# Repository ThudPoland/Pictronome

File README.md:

Metronome based on PIC16F microcontroller.

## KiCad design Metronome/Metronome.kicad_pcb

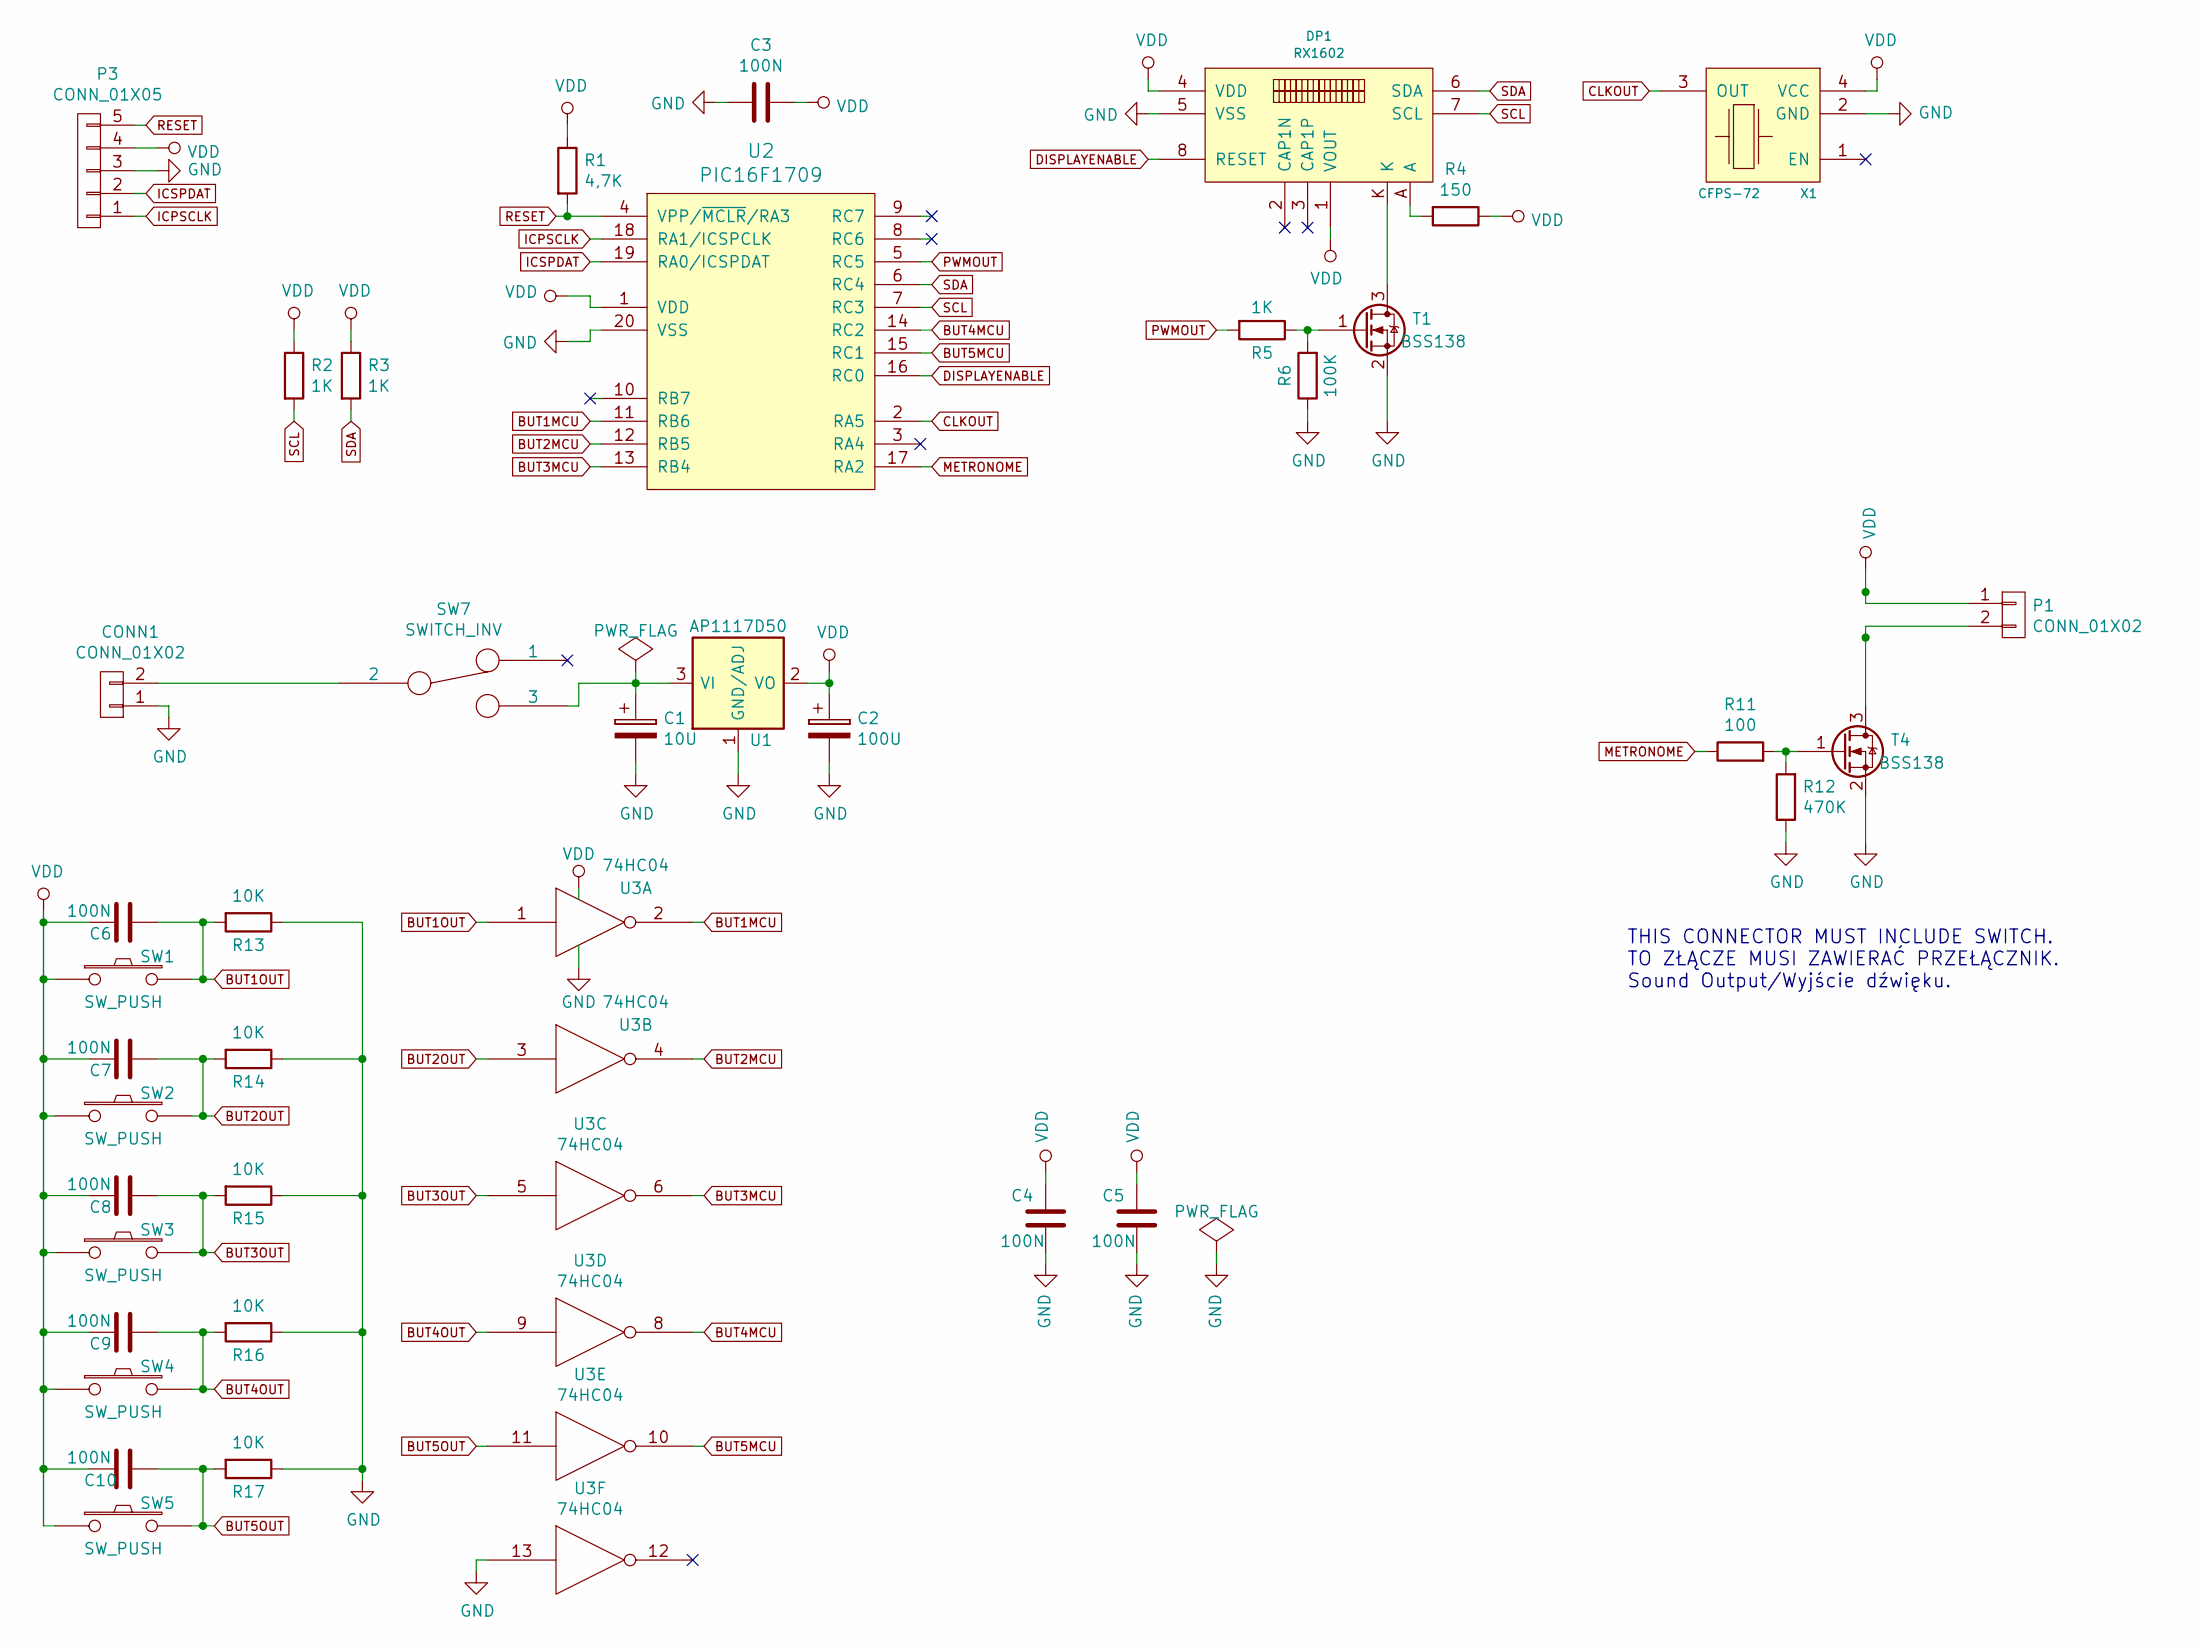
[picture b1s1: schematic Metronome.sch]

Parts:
C1: 10U; C_1206_HandSoldering
C2: 100U; TantalC_SizeC_EIA-6032_HandSoldering
C3, C4, C5, C6, C7, C8, C9, C10: 100N; R_0603_HandSoldering
CONN1: CONN_01X02; Pin_Header_Straight_1x02
DP1: RX1602
P1: CONN_01X02; Pin_Header_Straight_1x02
P3: CONN_01X05; Pin_Header_Straight_1x05
R1: 4,7K; R_0603_HandSoldering
R2, R3, R5: 1K; R_0603_HandSoldering
R4: 150; R_0603_HandSoldering
R6: 100K; R_0603_HandSoldering
R11: 100; R_0603_HandSoldering
R12: 470K; R_0603_HandSoldering
R13, R14, R15, R16, R17: 10K; R_0603_HandSoldering
SW1, SW2, SW3, SW4: SW_PUSH; TACT_SW3.3PER6
SW5: SW_PUSH; Pin_Header_Straight_1x02
SW7: SWITCH_INV; Pin_Header_Straight_1x03
T1, T4: BSS138; SOT-23_Handsoldering
U1: AP1117D50; SOT-223
U2: PIC16F1709; SSOP-20_5.3x7.2mm_Pitch0.65mm
U3: 74HC04; SOIC-14_N
X1: CFPS-72

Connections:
BUT1MCU: U2.11 (RB6), U3.2
BUT1OUT: C6.1, R13.2, SW1.2, U3.1
BUT2MCU: U2.12 (RB5), U3.4
BUT2OUT: C7.1, R14.2, SW2.2, U3.3
BUT3MCU: U2.13 (RB4), U3.6
BUT3OUT: C8.1, R15.2, SW3.2, U3.5
BUT4MCU: U2.14 (RC2), U3.8
BUT4OUT: C9.1, R16.2, SW4.2, U3.9
BUT5MCU: U2.15 (RC1), U3.10
BUT5OUT: C10.1, R17.2, SW5.2, U3.11
CLKOUT: U2.2 (RA5), X1.3 (OUT)
DISPLAYENABLE: DP1.8 (RESET), U2.16 (RC0)
GND: C1.2, C2.2, C3.2, C4.2, C5.2, CONN1.1, DP1.5 (VSS), P3.3, R6.1, R12.1, R13.1, R14.1, R15.1, R16.1, R17.1, T1.2 (S), T4.2 (S), U1.1 (GND/ADJ), U2.20 (VSS), U3.7 (GND), U3.13, X1.2 (GND)
ICPSCLK: P3.1, U2.18 (RA1/ICSPCLK)
ICSPDAT: P3.2, U2.19 (RA0/ICSPDAT)
METRONOME: R11.1, U2.17 (RA2)
unnamed: C1.1, SW7.3, U1.3 (VI)
unnamed: CONN1.2, SW7.2
unnamed: DP1.A, R4.2
unnamed: DP1.K, T1.3 (D)
unnamed: P1.2, T4.3 (D)
unnamed: R5.1, R6.2, T1.1 (G)
unnamed: R11.2, R12.2, T4.1 (G)
PWMOUT: R5.2, U2.5 (RC5)
RESET: P3.5, R1.2, U2.4 (VPP/~MCLR~/RA3)
SCL: DP1.7 (SCL), R2.2, U2.7 (RC3)
SDA: DP1.6 (SDA), R3.2, U2.6 (RC4)
VCC: C2.1, C3.1, C4.1, C5.1, C6.2, C7.2, C8.2, C9.2, C10.2, DP1.1 (VOUT), DP1.4 (VDD), P1.1, P3.4, R1.1, R2.1, R3.1, R4.1, SW1.1, SW2.1, SW3.1, SW4.1, SW5.1, U1.2 (VO), U2.1 (VDD), U3.14 (VCC), X1.4 (VCC)

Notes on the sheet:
THIS CONNECTOR MUST INCLUDE SWITCH. TO ZŁĄCZE MUSI ZAWIERAĆ PRZEŁĄCZNIK. Sound Output/Wyjście dźwięku.

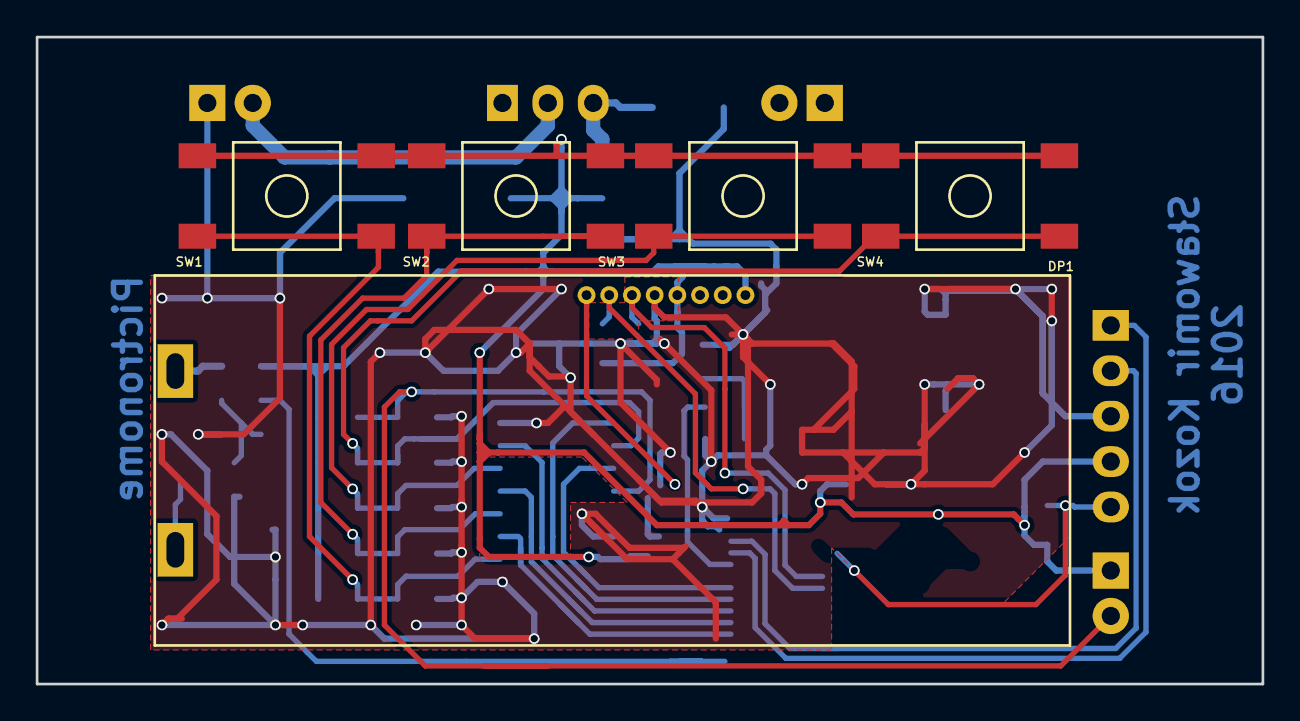
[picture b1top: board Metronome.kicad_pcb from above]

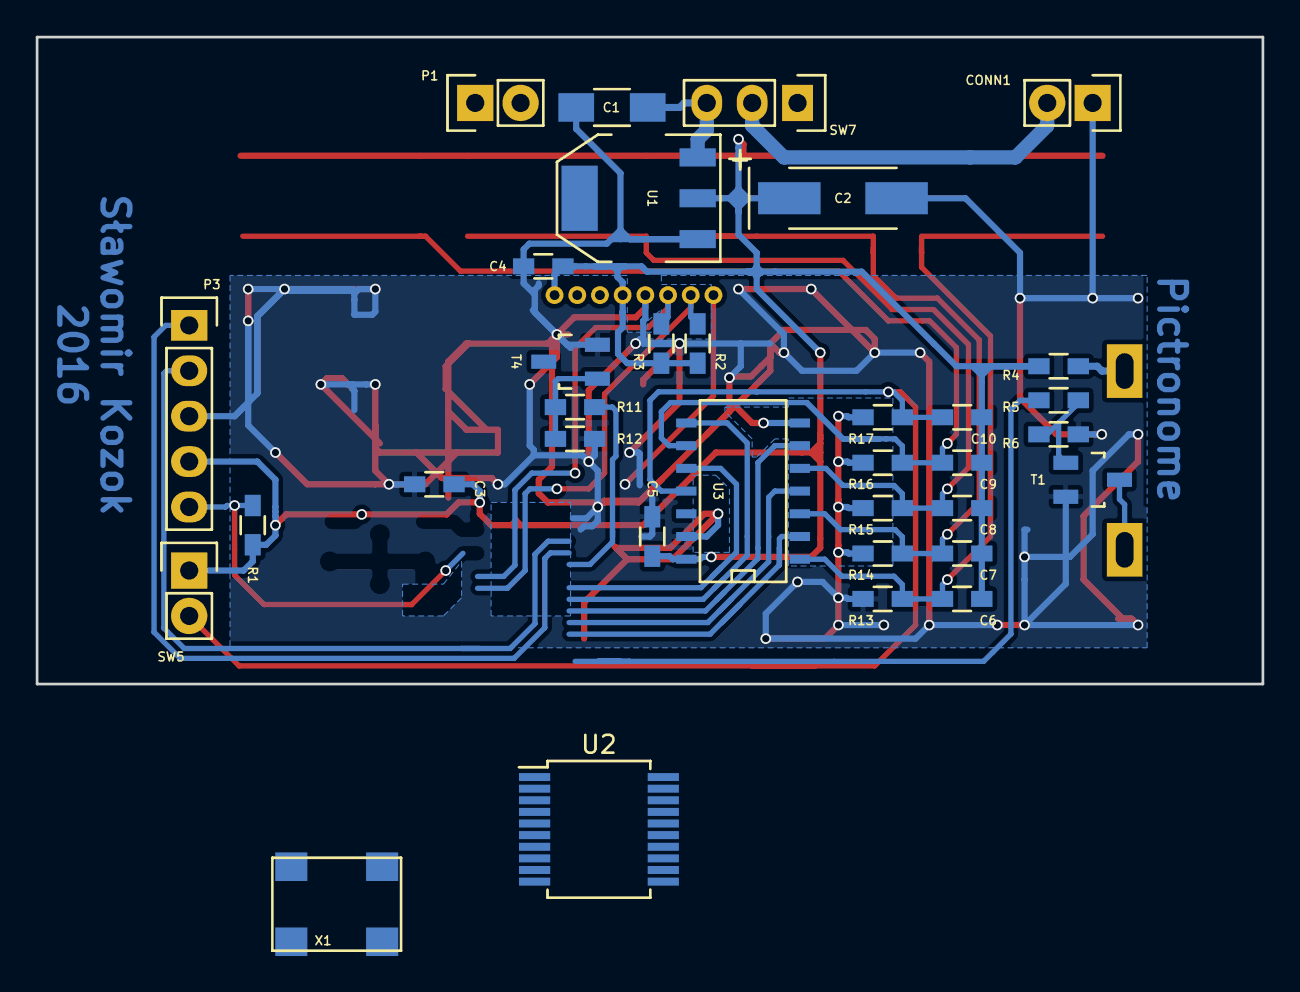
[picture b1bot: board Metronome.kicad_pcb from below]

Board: 2 copper layers, 68.6 x 36.2 mm, 39 parts (34 on the bottom side), 28 nets.

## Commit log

2017-02-19 Copy
    First commit containing copy from private repo.
2017-02-22 PCB Simplification
    SOme elements on PCB are unnecessary.
2017-02-22 Deleting unnecessary traces on PCB
2017-02-22 Fixes on PCB
    New PCB version is not yet ready.
2017-03-06 Adding SysTick for PIC
2017-03-22 Buzzer preparation
2017-03-22 Project tree repair
2017-03-22 Buzzer is working fine
    Buzzer, after modifications, is working as expected.
2017-03-25 Added entries for menu
2017-04-11 Project preparation for interactive menu
2017-04-12 Added basic navigation options
    COde must be checked.
2017-04-12 Entries bug fix
2017-04-12 Working navigation
    Working navigation between 4 sections.
2017-04-17 Small modifications in structures code.
2017-04-17 SendTextToFirstLine refactor
    Using only communication data.
2017-04-17 Memory usage refactor
    Using dedicated buffer for I2C.
2017-04-17 Clear display fix.
2017-04-17 Serious transmission bug to fix.
2017-05-10 I2C Display transimssion bug repair.
    Fixed sending data by I2C - deleted 1 unnecessary byte.
2017-05-10 Menu on LCD Display refactor
2017-05-10 Refactor
    Refactoring function names, added new functions for navigation,
2017-05-10 Function pointers simplification
    Function pointers could be simplier beacuse of using data source for each menu entry.
2017-05-11 Some minor changes
    -Added utils file.
    -Decreased needed RAM amount.
    -First menu function preparation.
2017-05-14 Button function working under menu
    -Implemented metronome toggle function init
    -Tested toggle button function
2017-05-16 Fixes + removal
    -Fixed -buzzer not shutting down sometimes
    -SoftPWM removal (it's too heavy for processing)
2017-05-16 Working PWM
    -Working PWM3
    -PPS can be changed multiple times
2017-05-16 Added setting PWM function
2017-07-19 Added brightness child menu.
2017-07-20 Working bar.
2017-07-20 Working tempo on UI
2017-07-23 GUI refresh timer
2017-07-23 Revert "GUI refresh timer"
    This reverts commit cd21fc6d886d2dcff25ca39c846619bdf2eeb6b4.
